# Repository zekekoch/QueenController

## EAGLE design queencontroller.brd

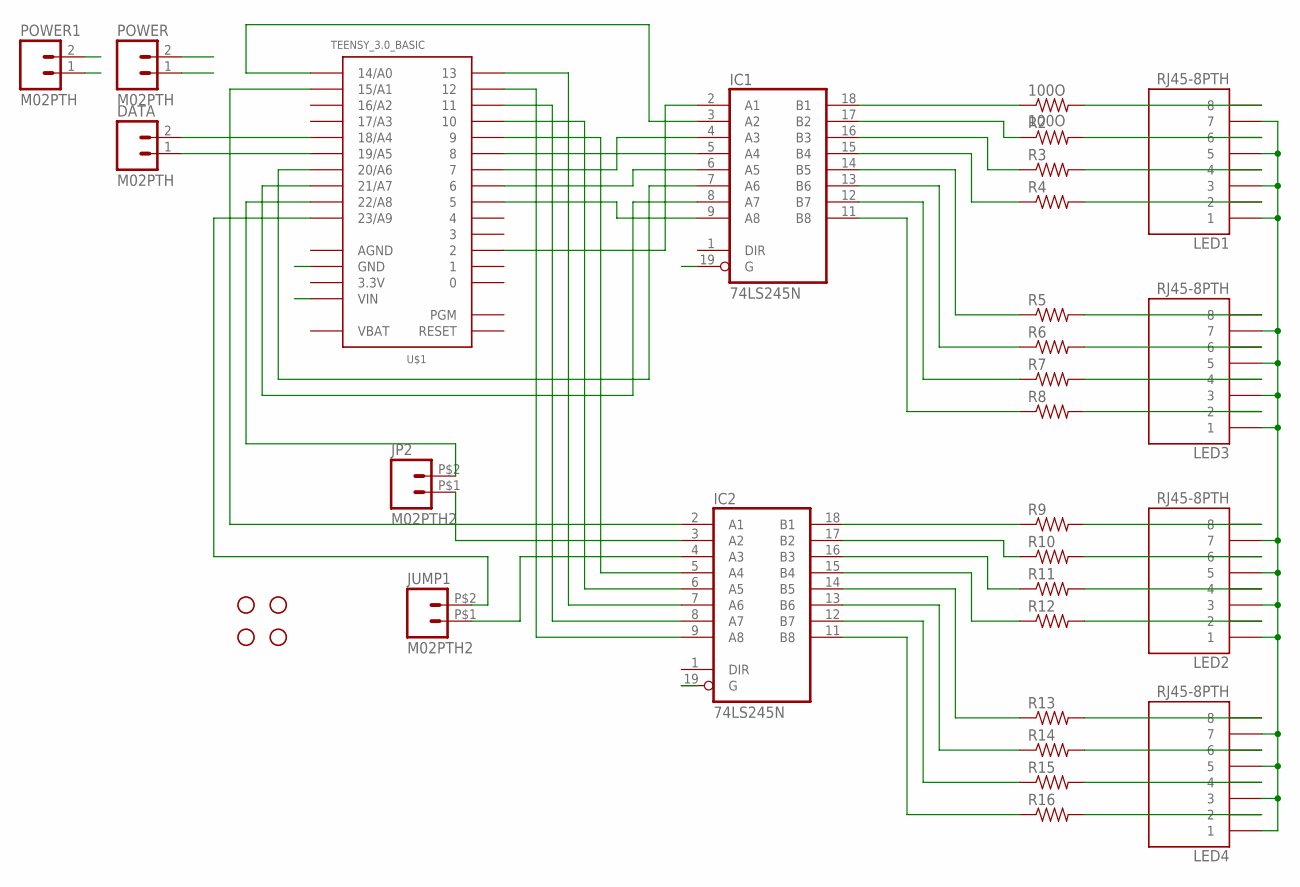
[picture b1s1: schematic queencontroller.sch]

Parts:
100O: 100O; 1206
DATA: M02PTH; 1X02
IC1, IC2: 74LS245N; DIL20
JP2: M02PTH2; 1X02_BIG
JUMP1: M02PTH2; 1X02_BIG
LED1, LED2, LED3, LED4: RJ45-8PTH; RJ45-8
POWER, POWER1: M02PTH; 1X02
R2, R3, R4, R5, R6, R7, R8, R9, R10, R11, R12, R13, R14, R15, R16: RESISTOR1206; 1206
STANDOFF1, STANDOFF2, STANDOFF3, STANDOFF4: STAND-OFF
U$1: TEENSY_3.0_BASIC

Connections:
3.3V: U$1.3.3V, U$1.3.3V1 (3.3V)
AGND: U$1.AGND
GND: IC1.10 (GND), IC1.19 (G), IC2.10 (GND), IC2.19 (G), LED1.1, LED1.3, LED1.5, LED1.7, LED2.1, LED2.3, LED2.5, LED2.7, LED3.1, LED3.3, LED3.5, LED3.7, LED4.1, LED4.3, LED4.5, LED4.7, POWER.1, POWER1.1, U$1.GND, U$1.GND1 (GND)
JMP1: JUMP1.P$2 (2), U$1.23/A9
JMP2: JP2.P$2 (2), U$1.22/A8
unnamed: 100O.2, LED1.8
unnamed: LED1.6, R2.2
unnamed: LED1.4, R3.2
unnamed: LED1.2, R4.2
unnamed: LED3.8, R5.2
unnamed: LED3.6, R6.2
unnamed: LED3.4, R7.2
unnamed: LED3.2, R8.2
unnamed: LED2.8, R9.2
unnamed: LED2.6, R10.2
unnamed: LED2.4, R11.2
unnamed: LED2.2, R12.2
unnamed: LED4.8, R13.2
unnamed: LED4.6, R14.2
unnamed: LED4.4, R15.2
unnamed: LED4.2, R16.2
unnamed: IC1.2 (A1), U$1.2
unnamed: IC1.3 (A2), U$1.14/A0
unnamed: IC1.4 (A3), U$1.7
unnamed: IC1.5 (A4), U$1.8
unnamed: IC1.6 (A5), U$1.6
unnamed: IC1.7 (A6), U$1.20/A6
unnamed: IC1.8 (A7), U$1.21/A7
unnamed: IC1.9 (A8), U$1.5
unnamed: IC2.2 (A1), U$1.15/A1
unnamed: IC2.3 (A2), JP2.P$1 (1)
unnamed: IC2.4 (A3), JUMP1.P$1 (1)
unnamed: IC2.5 (A4), U$1.9
unnamed: IC2.6 (A5), U$1.10
unnamed: IC2.7 (A6), U$1.13
unnamed: IC2.8 (A7), U$1.11
unnamed: IC2.9 (A8), U$1.12
unnamed: 100O.1, IC1.18 (B1)
unnamed: IC1.17 (B2), R2.1
unnamed: IC1.16 (B3), R3.1
unnamed: IC1.15 (B4), R4.1
unnamed: IC1.14 (B5), R5.1
unnamed: IC1.13 (B6), R6.1
unnamed: IC1.12 (B7), R7.1
unnamed: IC1.11 (B8), R8.1
unnamed: IC2.18 (B1), R9.1
unnamed: IC2.17 (B2), R10.1
unnamed: IC2.16 (B3), R11.1
unnamed: IC2.15 (B4), R12.1
unnamed: IC2.14 (B5), R13.1
unnamed: IC2.13 (B6), R14.1
unnamed: IC2.12 (B7), R15.1
unnamed: IC2.11 (B8), R16.1
SCL: DATA.1, U$1.19/A5
SDA: DATA.2, U$1.18/A4
VBAT: U$1.VBAT
VCC: IC1.20 (VCC), IC2.20 (VCC), POWER.2, POWER1.2, U$1.VIN

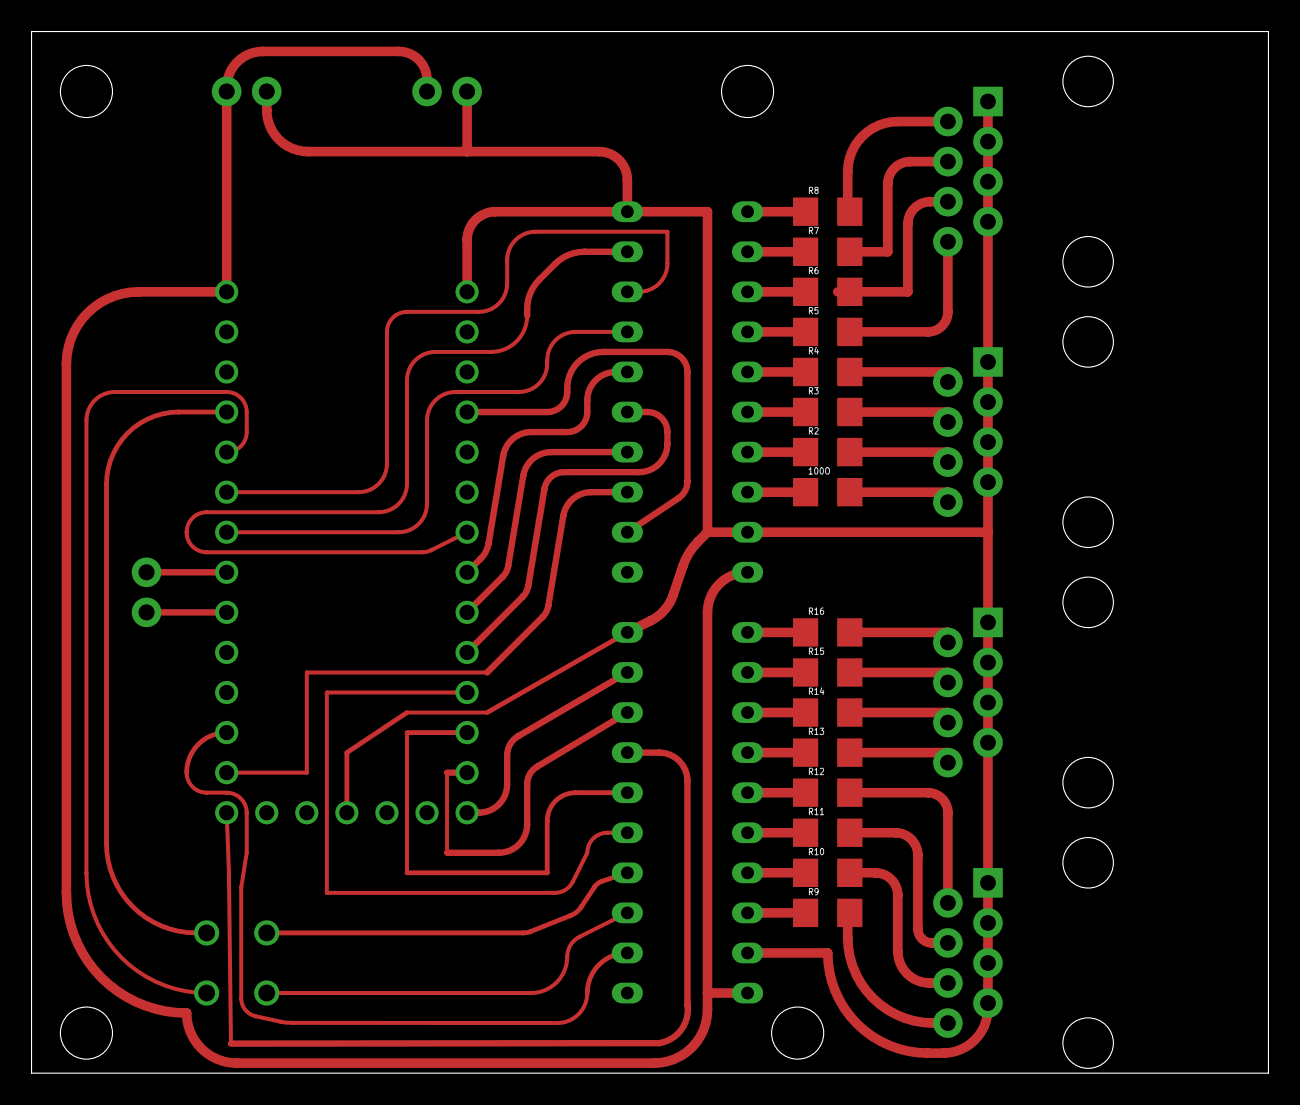
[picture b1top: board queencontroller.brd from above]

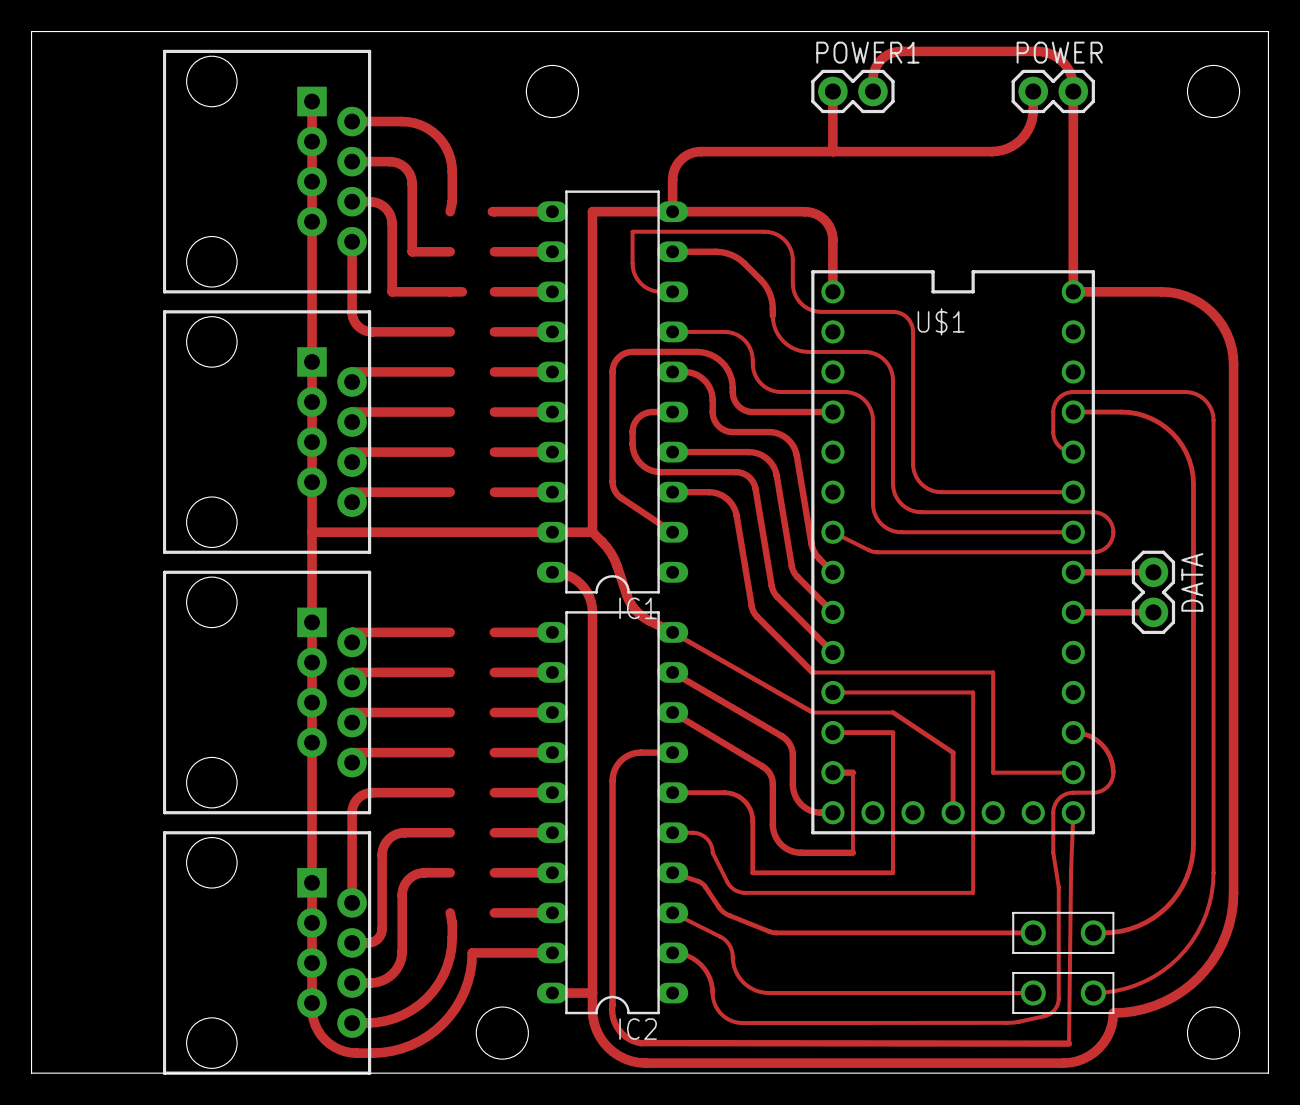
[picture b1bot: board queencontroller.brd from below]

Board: 2 copper layers, 78.4 x 66.0 mm, 32 parts (12 on the bottom side), 55 nets.

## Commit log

2015-09-29 Teensy 3.x to 16 ws2812 strips
    PCB to control 16 WS2812 Lights from one Teensy 3.x

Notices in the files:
parts and their libraries:
SparkFun-Connectors: Licensing: Creative Commons ShareAlike 4.0 International - https://creativecommons.org/licenses/by-sa/4.0
